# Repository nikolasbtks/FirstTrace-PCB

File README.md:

# FirstTrace

## Description

This project demonstrates a custom 2-layer PCB containing the STM32F103C8T6 microcontroller. This board can be used for embedded development using GPIO and SWD Headers.

## Components

1. Microcontroller: STM32F103C8T6
   - 20 KB SRAM and 64 KB Flash
   - 72 MHz clock speed 
   
2. USB Connectivity:
   - USB Micro-B for data and power 
   - USBLC6-2SC6 for ESD protection

3. Power Supply: AMS1117-3.3 
   - Voltage regulator for stable 3.3V output
  
4. Headers:
   - SWD headers for debugging and programming
   - GPIO headers for external connections
 
5. External Crystal Clock:
   - 16 MHz clock speed

## Disclaimer

This project is currently in **testing phase**. The provided documentation is shared for prototyping and learning purposes. If you choose to manufacture and use the board, please proceed with care, as it has not yet been fully validated.

## Schematic and PCB Design

The board was designed using KiCad. Files from the PCB design can be found in the **hardware** folder for board manufacture. This folder includes:

- PCB Schematic 
- PCB Layout
- Gerber files
- Assembly files

Below is a 3D render of the PCB design:

## How to Use

1. Power the board
   - Use a USB Micro cable to power the board.
   
2. Microcontroller Programming:
   - Use STM32CubeIDE to program the microcontroller.
   - Use an SWD debugger, such as ST-Link, to the SWD headers.

3. GPIO Access
   - Use the GPIO headers to connect peripherals.

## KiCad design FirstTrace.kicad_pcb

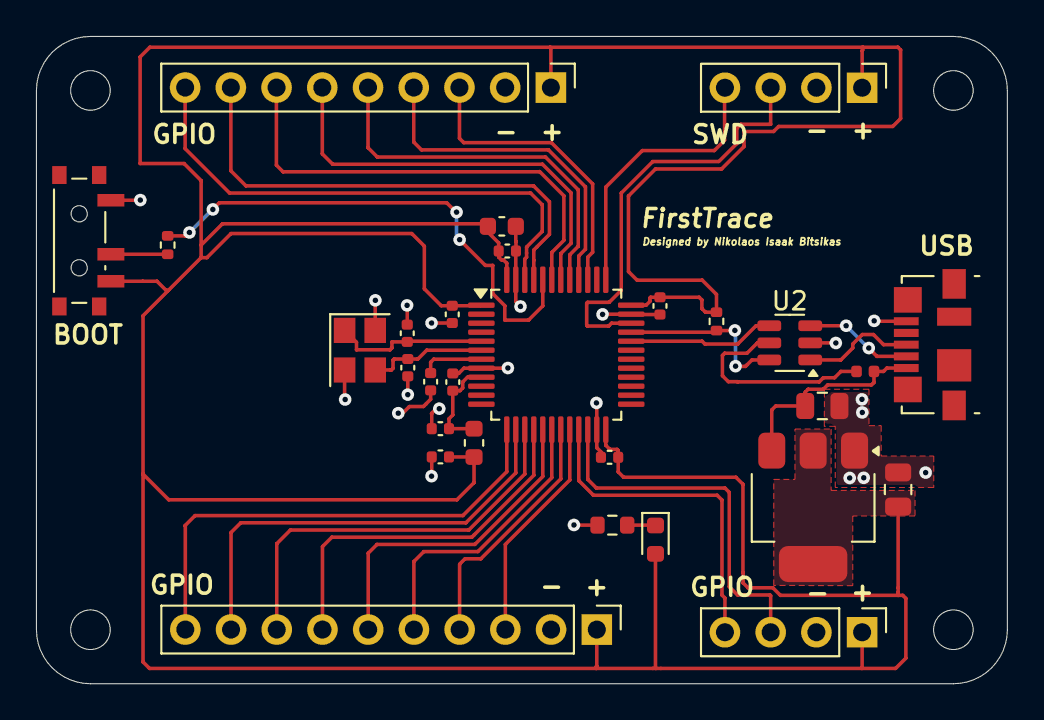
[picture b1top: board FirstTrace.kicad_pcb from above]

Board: 2 copper layers, 53.9 x 36.0 mm, 33 parts (0 on the bottom side), 34 nets.

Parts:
C1, C2, C3, C4, C6: 100n; C_0402_1005Metric
C5: 4.7u; C_0603_1608Metric
C7, C8: 10p; C_0402_1005Metric
C9: 10n; C_0402_1005Metric
C10, C11: 1u; C_0402_1005Metric
C12, C13: 22u; C_0805_2012Metric
D1: Green LED; LED_0603_1608Metric
F1: 500mA; Fuse_0402_1005Metric
FB1: FerriteBead; L_0603_1608Metric
H1, H2, H3, H4: MountingHole; MountingHole_2.2mm_M2
J1: USB_B_Micro; USB_Micro-B_Molex_47346-0001
J2, J4: Conn_01x04_Pin; PinHeader_1x04_P2.54mm_Vertical
J3: Conn_01x09_Pin; PinHeader_1x09_P2.54mm_Vertical
J5: Conn_01x10_Pin; PinHeader_1x10_P2.54mm_Vertical
R1: 10k; R_0402_1005Metric
R2: 1k5; R_0402_1005Metric
R3: 100R; R_0603_1608Metric
SW1: SW_SPDT; SW_SPDT_PCM12
U1: STM32F103C8Tx; LQFP-48_7x7mm_P0.5mm
U2: USBLC6-2SC6; SOT-23-6
U3: AMS1117-3.3; SOT-223-3_TabPin2
Y1: 16MHz; Crystal_SMD_3225-4Pin_3.2x2.5mm

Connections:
+3.3V: C1.1, C2.1, C3.1, C4.1, C5.1, C11.1, C13.1, D1.2 (A), FB1.2, J2.1, J3.1, J4.1, J5.1, R2.1, SW1.3 (C), U1.1 (VBAT), U1.24 (VDD), U1.36 (VDD), U1.48 (VDD), U3.2 (VO)
+3.3VA: C9.1, C10.1, FB1.1, U1.9 (VDDA)
+5V: F1.2, U2.5 (VBUS)
/BOOT0: R1.2, U1.44 (BOOT0)
/HSE_IN: C7.1, U1.5 (PD0), Y1.1
/HSE_OUT: C8.1, U1.6 (PD1), Y1.3
/NRST: C6.1, U1.7 (NRST)
/SW_BOOT0: R1.1, SW1.2 (B)
D+: J1.3 (D+), U2.1 (I/O1)
D-: J1.2 (D-), U2.3 (I/O2)
GND: C1.2, C2.2, C3.2, C4.2, C5.2, C6.2, C7.2, C8.2, C9.2, C10.2, C11.2, C12.2, C13.2, J1.5 (GND), J2.2, J3.2, J4.2, J5.2, R3.2, SW1.1 (A), U1.8 (VSSA), U1.23 (VSS), U1.35 (VSS), U1.47 (VSS), U2.2 (GND), U3.1 (GND), Y1.2, Y1.4
unnamed: D1.1 (K), R3.1
PA3: J5.10, U1.13 (PA3)
PA4: J5.9, U1.14 (PA4)
PA5: J5.8, U1.15 (PA5)
PA6: J5.7, U1.16 (PA6)
PA7: J5.6, U1.17 (PA7)
PB0: J5.5, U1.18 (PB0)
PB1: J5.4, U1.19 (PB1)
PB2: J5.3, U1.20 (PB2)
PB3: J3.3, U1.39 (PB3)
PB4: J3.4, U1.40 (PB4)
PB5: J3.5, U1.41 (PB5)
PB6: J3.6, U1.42 (PB6)
PB7: J3.7, U1.43 (PB7)
PB8: J3.8, U1.45 (PB8)
PB9: J3.9, U1.46 (PB9)
PB10: J4.4, U1.21 (PB10)
PB11: J4.3, U1.22 (PB11)
SWCLK: J2.4, U1.37 (PA14)
SWDIO: J2.3, U1.34 (PA13)
USB_D+: R2.2, U1.33 (PA12), U2.6 (I/O1)
USB_D-: U1.32 (PA11), U2.4 (I/O2)
VBUS: C12.1, F1.1, J1.1 (VBUS), U3.3 (VI)
